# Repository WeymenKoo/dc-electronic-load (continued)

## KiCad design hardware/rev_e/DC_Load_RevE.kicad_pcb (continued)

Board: 2 copper layers, 223 parts (1 on the bottom side), 119 nets, no tracks yet.

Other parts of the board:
H1, H2, H3, H4, H5, H6, H7, H8: MountingHole_3.2mm_M3
HA1, HA2, HA3, HA4: ScrewAccess_D7

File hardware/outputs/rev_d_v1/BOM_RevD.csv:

"Refs","Value","Footprint","MPN","Tolerance","Qty"
"C1,C2,C11,C18,C32","1uF","Capacitor_SMD:C_0603_1608Metric","","","5"
"C3,C6","10uF","Capacitor_SMD:C_0805_2012Metric","","","2"
"C4,C5,C8","22uF 25V","Capacitor_SMD:C_1206_3216Metric","","","3"
"C7,C57","10uF 25V","Capacitor_SMD:C_0805_2012Metric","","","2"
"C9,C12,C14-C17,C19-C21,C23,C27-C29,C31,C34,C51","100nF","Capacitor_SMD:C_0603_1608Metric","","","16"
"C10","1uF 25V","Capacitor_SMD:C_0603_1608Metric","","","1"
"C13","4.7uF","Capacitor_SMD:C_0805_2012Metric","","","1"
"C22","10uF X7R 10V","Capacitor_SMD:C_0805_2012Metric","","","1"
"C24,C25","10nF","Capacitor_SMD:C_0603_1608Metric","","","2"
"C30,C33","10nF C0G","Capacitor_SMD:C_0603_1608Metric","","","2"
"C35","47nF X7R","Capacitor_SMD:C_0603_1608Metric","","","1"
"C41,C42","10nF C0G 50V","Capacitor_SMD:C_0603_1608Metric","","","2"
"C52","100nF X7R","Capacitor_SMD:C_0603_1608Metric","","","1"
"C53-C56","100nF 50V","Capacitor_SMD:C_0603_1608Metric","","","4"
"C58","2.2uF 100V X7S","Capacitor_SMD:C_1206_3216Metric","","","1"
"C101,C201,C301,C401","1nF C0G 50V","Capacitor_SMD:C_0603_1608Metric","","","4"
"D1","USBLC6-2SC6","Package_TO_SOT_SMD:SOT-23-6","","","1"
"D2","LED green","LED_SMD:LED_0603_1608Metric","","","1"
"D3","SS34","Diode_SMD:D_SMA","","","1"
"D4","LED blue","LED_SMD:LED_0603_1608Metric","","","1"
"D5","CC","LED_SMD:LED_0603_1608Metric","","","1"
"D6","CV","LED_SMD:LED_0603_1608Metric","","","1"
"D7","CR","LED_SMD:LED_0603_1608Metric","","","1"
"D8","CP","LED_SMD:LED_0603_1608Metric","","","1"
"D9","BATT","LED_SMD:LED_0603_1608Metric","","","1"
"D10","ON","LED_SMD:LED_0603_1608Metric","","","1"
"D11","FAULT","LED_SMD:LED_0603_1608Metric","","","1"
"D12","REMOTE","LED_SMD:LED_0603_1608Metric","","","1"
"D41,D42","BAT54S","Package_TO_SOT_SMD:SOT-23","","","2"
"D43","BZX84C12","Package_TO_SOT_SMD:SOT-23","","","1"
"D44","BAT54C","Package_TO_SOT_SMD:SOT-23","","","1"
"D45,D101,D201,D301,D401","1N4148WS","Diode_SMD:D_SOD-323","","","5"
"D51","SMCJ70A TVS","Diode_SMD:D_SMC","","","1"
"D102,D202,D302,D402","BZX84C6V8","Package_TO_SOT_SMD:SOT-23","","","4"
"D103,D203,D303,D403","BZX84C15","Package_TO_SOT_SMD:SOT-23","","","4"
"DS1","VOLTS","Display_7Segment:CA56-12SRWA","CC56-12SRWA or 5641AS (common cathode)","","1"
"DS2","AMPS","Display_7Segment:CA56-12SRWA","CC56-12SRWA or 5641AS (common cathode)","","1"
"DS3","SET","Display_7Segment:CA56-12SRWA","CC56-12SRWA or 5641AS (common cathode)","","1"
"ENC1","PEC11L-4120K-S0020","Rotary_Encoder:RotaryEncoder_Alps_EC11E-Switch_Vertical_H20mm","Bourns PEC11L-4120K-S0020","","1"
"F1","15A 58VDC mini blade","Fuse:Fuseholder_Blade_Mini_Keystone_3568","Littelfuse 0997015.WXN","","1"
"J1","USB-C 16P","Connector_USB:USB_C_Receptacle_HRO_TYPE-C-31-M-12","HRO TYPE-C-31-M-12 (16 pin, USB 2.0)","","1"
"J2","FAN 4-pin","Connector_JST:JST_XH_B4B-XH-A_1x04_P2.50mm_Vertical","","","1"
"J3","SWD","Connector_PinHeader_2.54mm:PinHeader_1x05_P2.54mm_Vertical","","","1"
"J4","UART 3V3","Connector_PinHeader_2.54mm:PinHeader_1x03_P2.54mm_Vertical","","","1"
"J5","I2C OLED","Connector_PinHeader_2.54mm:PinHeader_1x04_P2.54mm_Vertical","","","1"
"J6","NTC 10k B3950","Connector_JST:JST_XH_B2B-XH-A_1x02_P2.50mm_Vertical","","","1"
"J7","DUT+","Connector_Wire:SolderWire-2.5sqmm_1x01_D2.4mm_OD3.6mm","","","1"
"J8","DUT-","Connector_Wire:SolderWire-2.5sqmm_1x01_D2.4mm_OD3.6mm","","","1"
"J9","SENSE","Connector_JST:JST_XH_B2B-XH-A_1x02_P2.50mm_Vertical","","","1"
"L1","10uH 2A","Inductor_SMD:L_Bourns_SRN6045TA","SRN6045TA-100M","","1"
"NT1","STAR","NetTie:NetTie-2_SMD_Pad2.0mm","","","1"
"PS1","B0512S-1WR3","dcload:SIP-4_P2.54mm_DCDC_1W","Mornsun B0512S-1WR3 (alt: Murata NXE1S0512MC)","","1"
"Q1","AO3401A","Package_TO_SOT_SMD:SOT-23","","","1"
"Q2,Q3,Q11-Q13","2N7002","Package_TO_SOT_SMD:SOT-23","","","5"
"Q101,Q201,Q301,Q401","IRFP250NPBF","Package_TO_SOT_THT:TO-247-3_Vertical","IRFP250NPBF","","4"
"R1,R2","5.1k","Resistor_SMD:R_0603_1608Metric","","1%","2"
"R3,R10,R13,R16,R24,R33,R37","1k","Resistor_SMD:R_0603_1608Metric","","","7"
"R4","191k","Resistor_SMD:R_0603_1608Metric","","1%","1"
"R5,R54,R58,R62,R69","10.0k","Resistor_SMD:R_0603_1608Metric","","1%","5"
"R6,R8,R65,R105,R205,R305,R405","100k","Resistor_SMD:R_0603_1608Metric","","","7"
"R7,R9,R19-R23,R52,R56,R61,R64,R70","10k","Resistor_SMD:R_0603_1608Metric","","","12"
"R12","4.7R","Resistor_SMD:R_1206_3216Metric","","","1"
"R14,R15","4.7k","Resistor_SMD:R_0603_1608Metric","","","2"
"R17,R18","33k","Resistor_SMD:R_0603_1608Metric","","1%","2"
"R31","15k","Resistor_SMD:R_0603_1608Metric","","0.1%","1"
"R32","1k","Resistor_SMD:R_0603_1608Metric","","0.1%","1"
"R34,R35,R57","100k","Resistor_SMD:R_0603_1608Metric","","1%","3"
"R36,R66","10k","Resistor_SMD:R_0603_1608Metric","","1%","2"
"R41,R67","1M","Resistor_SMD:R_0603_1608Metric","","1%","2"
"R42,R46,R49","10k","Resistor_SMD:R_0603_1608Metric","","0.1%","3"
"R43","110k","Resistor_SMD:R_0603_1608Metric","","0.1%","1"
"R44,R50","1k","Resistor_SMD:R_0603_1608Metric","","1%","2"
"R45,R48","200k","Resistor_SMD:R_1206_3216Metric","","0.1%","2"
"R47","470k","Resistor_SMD:R_0603_1608Metric","","1%","1"
"R51","10.0k","Resistor_SMD:R_0603_1608Metric","","0.1%","1"
"R53","90.9k","Resistor_SMD:R_0603_1608Metric","","1%","1"
"R55","402k","Resistor_SMD:R_0603_1608Metric","","1%","1"
"R59","165k","Resistor_SMD:R_0603_1608Metric","","1%","1"
"R60","47k","Resistor_SMD:R_1206_3216Metric","","1%","1"
"R63","27.4k","Resistor_SMD:R_0603_1608Metric","","1%","1"
"R68","5.90k","Resistor_SMD:R_0603_1608Metric","","1%","1"
"R71","2.2R 1W","Resistor_SMD:R_2512_6332Metric","","1%","1"
"R72,R73","100R","Resistor_SMD:R_1206_3216Metric","","","2"
"R101,R201,R301,R401","4.7k","Resistor_SMD:R_0603_1608Metric","","1%","4"
"R102,R202,R302,R402","22M","Resistor_SMD:R_0603_1608Metric","","5%","4"
"R103,R203,R303,R403","3.3k","Resistor_SMD:R_0603_1608Metric","","1%","4"
"R104,R204,R304,R404","47","Resistor_SMD:R_0603_1608Metric","","1%","4"
"R106,R107,R206,R207,R306,R307,R406,R407","0R2 1W","Resistor_SMD:R_2512_6332Metric","","1%","8"
"R108,R208,R308,R408","10k","Resistor_SMD:R_0603_1608Metric","","0.1% 25ppm","4"
"SW1","RESET","Button_Switch_THT:SW_PUSH_6mm","","","1"
"SW2","BOOT","Button_Switch_THT:SW_PUSH_6mm","","","1"
"SW3","ON/OFF","Button_Switch_THT:SW_PUSH_6mm","","","1"
"SW4","MODE","Button_Switch_THT:SW_PUSH_6mm","","","1"
"SW5","MENU","Button_Switch_THT:SW_PUSH_6mm","","","1"
"TP11","VSET","TestPoint:TestPoint_THTPad_D1.5mm_Drill0.7mm","","","1"
"TP21","ISEN_ADC","TestPoint:TestPoint_THTPad_D1.5mm_Drill0.7mm","","","1"
"TP22","VSEN_ADC","TestPoint:TestPoint_THTPad_D1.5mm_Drill0.7mm","","","1"
"TP31","CV_SET","TestPoint:TestPoint_THTPad_D1.5mm_Drill0.7mm","","","1"
"TP41","KILL","TestPoint:TestPoint_THTPad_D1.5mm_Drill0.7mm","","","1"
"TP51","DUT+","TestPoint:TestPoint_THTPad_D1.5mm_Drill0.7mm","","","1"
"TP52","DRAIN","TestPoint:TestPoint_THTPad_D1.5mm_Drill0.7mm","","","1"
"TP101,TP201,TP301,TP401","GATE","TestPoint:TestPoint_THTPad_D1.5mm_Drill0.7mm","","","4"
"TP102,TP202,TP302,TP402","SOURCE","TestPoint:TestPoint_THTPad_D1.5mm_Drill0.7mm","","","4"
"U1","AP2112K-3.3","Package_TO_SOT_SMD:SOT-23-5","","","1"
"U2","MT3608","Package_TO_SOT_SMD:SOT-23-6","","","1"
"U3","MCP1703A-5002","Package_TO_SOT_SMD:SOT-23","MCP1703AT-5002E/CB","","1"
"U4","STM32G0B1CBT6","Package_QFP:LQFP-48_7x7mm_P0.5mm","STM32G0B1CBT6","","1"
"U5,U6","MAX7219","Package_SO:SOIC-24W_7.5x15.4mm_P1.27mm","MAX7219CWG","","2"
"U7","74AHCT125","Package_SO:SOIC-14_3.9x8.7mm_P1.27mm","","","1"
"U8","ISO7761DW","Package_SO:SOIC-16W_7.5x10.3mm_P1.27mm","ISO7761DW (default-high outputs)","","1"
"U9","MCP4822","Package_SO:SOIC-8_3.9x4.9mm_P1.27mm","MCP4822-E/SN","","1"
"U10","ADS1118","Package_SO:TSSOP-10_3x3mm_P0.5mm","ADS1118IDGSR","","1"
"U11","LT1014","Package_SO:SOIC-16W_7.5x10.3mm_P1.27mm","","","1"
"U12,U13","LT1013","Package_SO:SOIC-8_3.9x4.9mm_P1.27mm","","","2"
"U14","LM339","Package_SO:SOIC-14_3.9x8.7mm_P1.27mm","","","1"

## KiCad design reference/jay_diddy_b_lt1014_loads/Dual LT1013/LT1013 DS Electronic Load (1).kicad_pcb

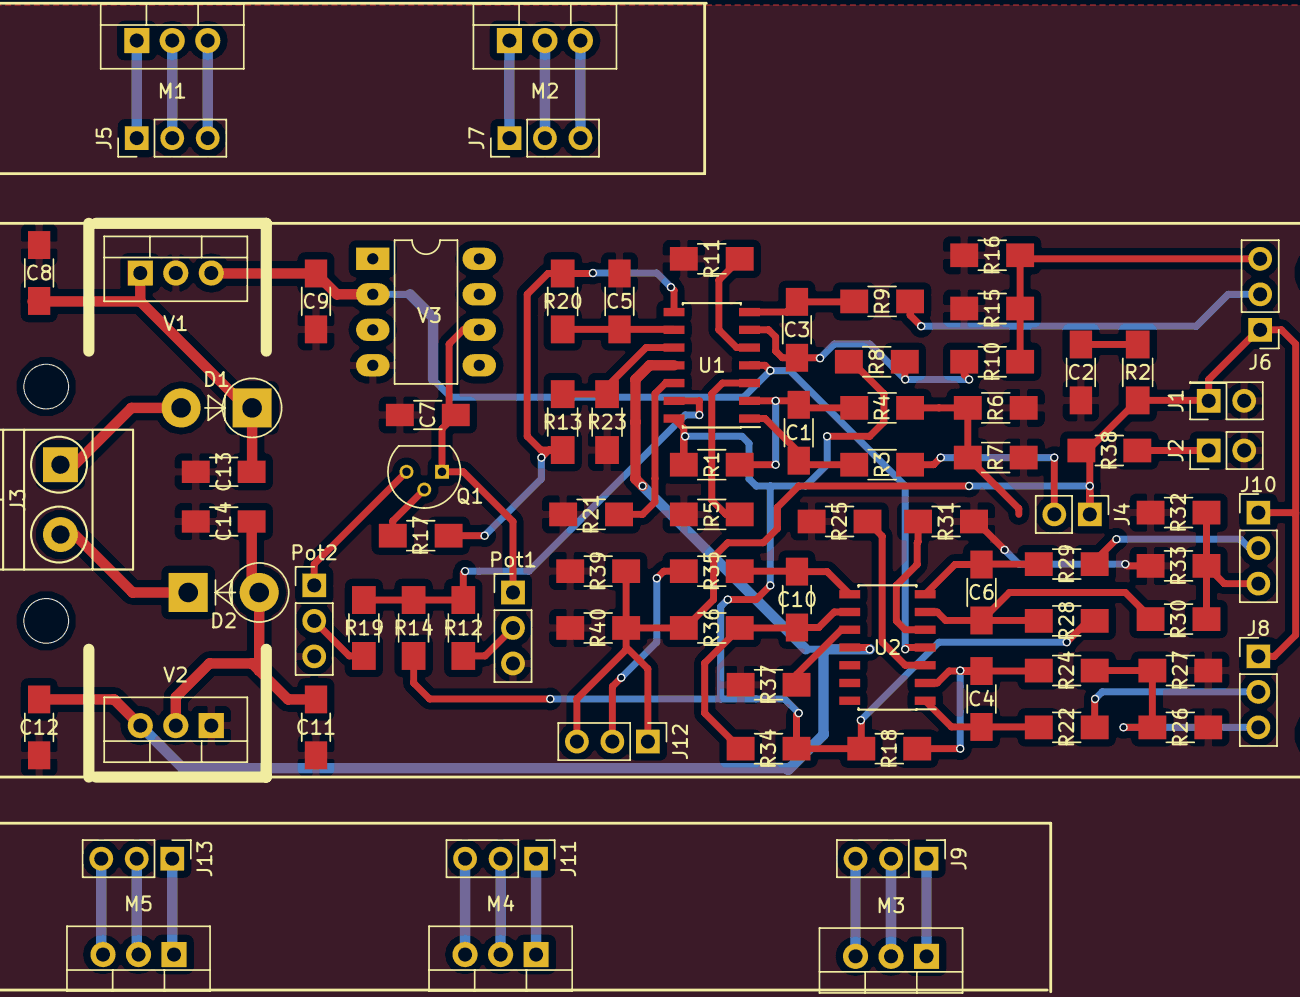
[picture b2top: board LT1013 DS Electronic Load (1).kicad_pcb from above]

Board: 2 copper layers, 82 parts (0 on the bottom side), 60 nets.

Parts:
C1, C3, C4, C6, C10: 220pF; C_1206_HandSoldering
C2, C11: 2.2uF; C_1206_HandSoldering
C5, C7, C9: 0.1uF; C_1206_HandSoldering
C8: 0.33uF; C_1206_HandSoldering
C12: 1uF; C_1206_HandSoldering
C13, C14: 220uF; C_1206_HandSoldering
D1: 1N4002; D_5W_P5.08mm_Vertical_AnodeUp
D2: 1N4002; D_5W_P5.08mm_Vertical_KathodeUp
J1: Conn_01x02; Socket_Strip_Straight_2x01_Pitch2.54mm
J2: Conn_01x02; Pin_Header_Straight_1x02_Pitch2.54mm
J3: Screw_Terminal_01x02; TerminalBlock_Pheonix_MKDS1.5-2pol
J4: Conn_01x03; Pin_Header_Straight_1x02_Pitch2.54mm
J5, J6, J7, J8, J9, J10, J11, J12, J13: Conn_01x03; Pin_Header_Straight_1x03_Pitch2.54mm
M1, M2, M3, M4, M5: IRF530; TO-220-3_Vertical
Pot1, Pot2: 10K; Pin_Header_Straight_1x03_Pitch2.54mm
Q1: 2N3906; TO-92_Molded_Narrow
R1, R8, R13, R18, R21, R28, R34: 33K; R_1206_HandSoldering
R2: 2.2; R_1206_HandSoldering
R3, R9, R22, R29, R35: 100; R_1206_HandSoldering
R4, R5, R10, R11, R24, R25, R30, R31, R36, R37: 3K3; R_1206_HandSoldering
R6, R7, R15, R16, R26, R27, R32, R33, R39, R40: 0.2; R_1206_HandSoldering
R12, R14, R19: 100K; R_1206_HandSoldering
R17, R20, R23: 15K; R_1206_HandSoldering
R38: 51R; R_1206_HandSoldering
U1, U2: LT1013; SOIC-14_3.9x8.7mm_Pitch1.27mm
V1: L7809; TO-220-3_Vertical
V2: LM7909_TO220; TO-220-3_Vertical
V3: LT1019_Voltage_Reference; DIP-8_W7.62mm_LongPads

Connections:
/+9V: C9.1, U1.4, U2.4, V1.3, V3.2
/-9v: C12.1, U1.11, U2.11, V2.3
/Vref: C7.1, Pot1.1, Q1.1, V3.6
GND: C2.2, C5.2, C7.2, C8.2, C9.2, C11.2, C12.2, C13.1, C14.2, J1.2, J2.2, Pot1.3, Pot2.3, R5.2, R6.2, R7.2, R11.2, R15.2, R16.2, R21.1, R23.2, R25.2, R26.2, R27.2, R31.2, R32.2, R33.2, R37.2, R39.2, R40.2, V1.2, V2.1, V3.4
unnamed: C1.1, R3.2, U1.1
unnamed: C1.2, R1.2, R4.1, U1.2
unnamed: C2.1, R2.2
unnamed: C3.1, R9.2, U1.7
unnamed: C3.2, R8.2, R10.1, U1.6
unnamed: C4.1, R22.2, U2.1
unnamed: C4.2, R18.2, R24.1, U2.2
unnamed: C5.1, R20.2, U1.9
unnamed: C6.1, R29.2, U2.7
unnamed: C6.2, R28.2, R30.1, U2.6
unnamed: C10.1, R35.2, U2.8
unnamed: C10.2, R34.2, R36.1, U2.9
unnamed: C11.1, C14.1, D2.2, V2.2
unnamed: C8.1, C13.2, D1.1, V1.1
unnamed: D1.2, J3.1
unnamed: D2.1, J3.2
unnamed: J1.1, J4.1, J6.1, J8.1, J10.1, J12.1, J12.3, R2.1, R36.2, R38.2, R39.1, R40.1
unnamed: J2.1, R38.1
unnamed: J4.2, R3.1
unnamed: R4.2, R6.1, R7.1
unnamed: J5.1, M1.1
unnamed: J5.2, M1.2
unnamed: J5.3, M1.3
unnamed: J6.2, R9.1
unnamed: J6.3, R10.2, R15.1, R16.1
unnamed: J7.1, M2.1
unnamed: J7.2, M2.2
unnamed: J7.3, M2.3
unnamed: J8.2, R22.1
unnamed: J8.3, R24.2, R26.1, R27.1
unnamed: J9.1, M3.1
unnamed: J9.2, M3.2
unnamed: J9.3, M3.3
unnamed: J10.2, R29.1
unnamed: J10.3, R30.2, R32.1, R33.1
unnamed: J11.1, M4.1
unnamed: J11.2, M4.2
unnamed: J11.3, M4.3
unnamed: J12.2, R35.1
unnamed: J13.1, M5.1
unnamed: J13.2, M5.2
unnamed: J13.3, M5.3
unnamed: Pot1.2, R12.2
unnamed: Pot2.1, Q1.3
unnamed: Pot2.2, R19.2
unnamed: Q1.2, R17.1
unnamed: R1.1, R8.1, R14.1, R18.1, R28.1, R34.1, U1.14
unnamed: R5.1, U1.3
unnamed: R11.1, U1.5
unnamed: R12.1, R14.2, R19.1, U1.13
unnamed: R13.1, R17.2, R20.1, U1.8
unnamed: R13.2, R23.1, U1.10
unnamed: R21.2, U1.12
unnamed: R25.1, U2.3
unnamed: R31.1, U2.5
unnamed: R37.1, U2.10

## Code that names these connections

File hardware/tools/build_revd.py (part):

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    esd.fpos = {'Reference': (103, 100), 'Value': (103, 103)}
    s.wire((70, dp2[1]), (70, 110), (86, 110), (86, esd.pin('3')[1]), esd.pin('3'), color=C_USB)
    s.wire((72, dm2[1]), (72, esd.pin('1')[1]), esd.pin('1'), color=C_USB)
    s.wire(esd.pin('6'), (112, esd.pin('6')[1]), color=C_USB); s.hier('USB_DM', 112, esd.pin('6')[1], ang=0, shape='bidirectional', color=C_USB)
    s.wire(esd.pin('4'), (112, esd.pin('4')[1]), color=C_USB); s.hier('USB_DP', 112, esd.pin('4')[1], ang=0, shape='bidirectional', color=C_USB)
    s.rail('VBUS', esd.pin('5')[0], esd.pin('5')[1]); s.rail('DGND', esd.pin('2')[0], esd.pin('2')[1])
    s.nc(*j.pin('A8')); s.nc(*j.pin('B8'))
    g, sh = j.pin('A1'), j.pin('SH')
    s.wire(g, (g[0], 112), (62, 112)); s.rail('DGND', g[0], 112); s.rail('FLAG', 62, 112)
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    s.begin_block('D   Ground star point and the isolation barrier rating', FILL_A)
    nt = s.part('Device:NetTie_2', 'NT1', 'STAR', 60, 190, fp='NetTie:NetTie-2_SMD_Pad2.0mm')
    nt.fpos = {'Reference': (60, 186.2, 'center'), 'Value': (60, 193.8, 'center')}
    s.wire(nt.pin('1'), (50, 190), (50, 196)); s.rail('AGND', 50, 196)
    s.wire(nt.pin('2'), (70, 190), (70, 196)); s.rail('PGND', 70, 196); s.rail('FLAG', 76, 190)
    s.wire((70, 190), (76, 190))
    s.note('AGND (analog reference) meets PGND (DUT minus, source\n'
           'resistors) ONLY at NT1. Place NT1 at the centre of the four\n'
           'Rs bottom pads: 1 mR between an Rs and NT1 is 10 mV at 10 A\n'
           '(4 % of full scale).\n\n'
           'Barrier: DGND side to AGND / PGND side. Rated 150 V DC\n'
           'working (IEC 60664-1 functional, PD2, material group IIIb:\n'
           '1.6 mm creepage; IPC-2221B B2: 0.7 mm). Board rule 4 mm,\n'
           'no copper crosses on any layer. ISO7761 (5 kVrms, 8 mm) and\n'
           'the 3 kVDC DC-DC exceed it by far. Float the load on a DUT\n'
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    u = s.ic('Regulator_Linear:AP2112K-3.3', 'U1', 'AP2112K-3.3', 192, y + 2.54, 10); u.fpos = {'Reference': (192, y - 9.5, 'center'), 'Value': (192, y - 6.5, 'center')}
    vin, en, gnd, vout = u.pin('1'), u.pin('3'), u.pin('2'), u.pin('5')
    s.wire(en, (180, en[1]), (180, y))
    s.rail('DGND', gnd[0], gnd[1]); s.nc(*u.pin('4'))
    s.wire(vout, (244, y), color=C_PWR); s.rail('+3V3', 244, y)
    c = s.cap('C2', '1uF', 210, y + 6); s.wire((210, y), top(c)); s.rail('DGND', 210, bot(c)[1])
    r = s.res('R3', '1k', 228, y + 6); s.wire((228, y), top(r))
    d = s.led('D2', 'LED green', 228, y + 16); s.wire(bot(r), d.pin('2')); s.wire(d.pin('1'), (228, y + 23)); s.rail('DGND', 228, y + 23)
    s.note('+3V3: MCU, isolator side 1, pull-ups, LED. 60 mA.', 170, 94)
    # ---- branch 2: 12 V fan supply
    y = 108
    s.wire((T, y), (210.19, y), color=C_PWR)
    c = s.cap('C3', '10uF', 172, y + 6, fp=C0805); s.wire((172, y), top(c)); s.rail('DGND', 172, bot(c)[1])
    u = s.ic('Regulator_Switching:MT3608', 'U2', 'MT3608', 200, y + 16, 10); u.fpos = {'Reference': (200, y + 5.5, 'center'), 'Value': (209.5, y + 24.5)}
    pin_in, pen, sw, fb, pgnd = u.pin('5'), u.pin('4'), u.pin('1'), u.pin('3'), u.pin('2')
    s.wire((190, y), (190, pin_in[1]), pin_in)
    l = s.part('Device:L', 'L1', '10uH 2A', 214, y, rot=90, fp='Inductor_SMD:L_Bourns_SRN6045TA', f={'MPN': 'SRN6045TA-100M'})
    l.fpos = {'Reference': (214, y - 2.6, 'center'), 'Value': (214, y + 3.3, 'center')}
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    rt = s.res('R4', '191k', 236, y + 7.27, tol='1%'); s.wire((236, y), top(rt))
    s.wire(fb, (236, fb[1])); s.wire(bot(rt), (236, fb[1]))
    rb = s.res('R5', '10.0k', 236, fb[1] + 7.46, tol='1%'); s.wire((236, fb[1]), top(rb)); s.rail('DGND', 236, bot(rb)[1])
    s.rail('DGND', pgnd[0], pgnd[1]); s.nc(*u.pin('6'))
    s.wire(pen, (188, pen[1]), (188, y + 32), (176, y + 32)); s.hier('FAN_EN', 176, y + 32, ang=180)
    rpd = s.res('R6', '100k', 188, y + 37); s.wire((188, y + 32), top(rpd)); s.rail('DGND', 188, bot(rpd)[1])
    s.note('+12V_FAN: 0.6 V x (1 + 191k / 10k) = 12.06 V, 0.3 A max = 0.8 A from USB.\nEN low: output sits at VBUS minus a diode and Q1 (block C) is off.', 170, 166)
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    rpu = s.res('R7', '10k', X0, Y0 - 10.81); s.rail('+12V_FAN', X0, top(rpu)[1])
    qn = s.fet(Q2N, 'Q2', '2N7002', X0 - 20, Y0 + 1)
    s.wire(gate, (X0, Y0 - 7), (qn.pin('3')[0], Y0 - 7), qn.pin('3'))
    s.rail('DGND', qn.pin('2')[0], qn.pin('2')[1])
    s.wire(qn.pin('1'), (X0 - 36, qn.pin('1')[1])); s.hier('FAN_EN', X0 - 36, qn.pin('1')[1], ang=180)
    rpd2 = s.res('R8', '100k', X0 - 30, Y0 + 7); s.wire((X0 - 30, qn.pin('1')[1]), top(rpd2)); s.rail('DGND', X0 - 30, bot(rpd2)[1])
    s.wire(p3, (X0 + 12, p3[1]), (X0 + 12, Y0 + 38), (X0 + 6, Y0 + 38))
    rpu2 = s.res('R9', '10k', X0 + 6, Y0 + 34.19, fl=True); s.rail('+3V3', X0 + 6, top(rpu2)[1])
    rs = s.res('R10', '1k', X0 - 4, Y0 + 38, h=True); s.wire((X0 + 6, Y0 + 38), rgt(rs)); s.wire(lft(rs), (X0 - 18, Y0 + 38)); s.hier('FAN_TACH', X0 - 18, Y0 + 38, ang=180, shape='output')
    s.wire(p4, (X0 + 16, p4[1]), (X0 + 16, Y0 + 60))
    qpwm = s.fet(Q2N, 'Q3', '2N7002', X0 + 13.46, Y0 + 65.08)
    s.rail('DGND', qpwm.pin('2')[0], qpwm.pin('2')[1])
    s.wire(qpwm.pin('1'), (X0 - 18, qpwm.pin('1')[1])); s.hier('FAN_PWM', X0 - 18, qpwm.pin('1')[1], ang=180)
    rpu3 = s.res('R11', '10k DNP', X0 + 6, Y0 + 56.19, dnp=True, fl=True); s.wire((X0 + 16, Y0 + 60), bot(rpu3)); s.rail('VBUS', X0 + 6, top(rpu3)[1])
    s.note('J2 = PC fan pinout: 1 GND, 2 +12 V,\n'
           '3 tach (open collector, pulled to 3.3 V),\n'
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    H, L = 'hier', 'label'
    # name -> (label, kind, shape, colour)
    plan = {
        'PA0': ('CC1_SENSE', H, 'input', None), 'PA1': ('CC2_SENSE', H, 'input', None),
        'PA4': ('~{CS_DAC}', H, 'output', C_SPI), 'PA5': ('SPI1_SCK', H, 'output', C_SPI), 'PA6': ('SPI1_MISO', H, 'input', C_SPI), 'PA7': ('SPI1_MOSI', H, 'output', C_SPI),
        'PB0': ('~{CS_ADC}', H, 'output', C_SPI), 'PB1': ('LOAD_OFF', H, 'output', C_PROT),
        'PB12': ('~{DISP_CS}', H, 'output', None), 'PB13': ('SPI2_SCK', H, 'output', None), 'PB15': ('SPI2_MOSI', H, 'output', None),
        'PC6': ('LED_STATUS', L, None, None), 'PA9/UCPD1_DBCC1': ('UART_TX', L, None, None), 'PA10/UCPD1_DBCC2': ('UART_RX', L, None, None),
        'PA9/PA11': ('USB_DM', H, 'bidirectional', C_USB), 'PA10/PA12': ('USB_DP', H, 'bidirectional', C_USB),
        'PA13': ('SWDIO', L, None, None), 'PA14': ('SWCLK_BOOT0', L, None, None),
        'PB3': ('ENC_SW', H, 'input', None), 'PB4': ('ENC_A', H, 'input', None), 'PB5': ('ENC_B', H, 'input', None),
        'PB6': ('I2C_SCL', L, None, None), 'PB7': ('I2C_SDA', L, None, None), 'PB8': ('FAN_TACH', H, 'input', None), 'PB9': ('FAN_PWM', H, 'output', None),
        'PD0': ('BTN_ON', H, 'input', None), 'PD1': ('BTN_MODE', H, 'input', None), 'PD2': ('BTN_MENU', H, 'input', None),
        'PD3': ('FAN_EN', H, 'output', None), 'PF2': ('NRST', L, None, None),
    }
    names = {}
    for sub in find(u.sym, 'symbol'):
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    s.wire(vref, (vref[0] - 8, vref[1]), (vref[0] - 8, vref[1] - 8), color=C_PWR); s.rail('+3V3', vref[0] - 8, vref[1] - 8)
    s.rail('DGND', vss[0], vss[1])
    s.note('Pin plan (STM32G0B1CBT6, LQFP48)\n'
           'SPI1   PA5 SCK, PA6 MISO, PA7 MOSI, PA4 /CS DAC, PB0 /CS ADC, PB1 LOAD_OFF (isolator)\n'
           'SPI2   PB13 SCK, PB15 MOSI, PB12 /CS = MAX7219 LOAD (display chain, via 74AHCT125)\n'
           'TIM3   PB4 / PB5 encoder, PB3 push.  TIM17 PB9 fan PWM, TIM16 PB8 tach, PD3 FAN_EN\n'
           'ADC    PA0 / PA1 = CC1 / CC2.  USB PA11 DM, PA12 DP, crystal-less (CRS)\n'
           'USART1 PA9 / PA10 debug.  I2C1 PB6 / PB7 OLED.  PD0 ON/OFF, PD1 MODE, PD2 MENU, PC6 LED\n'
           'Why not the STM32F103RBT6 of Rev B: no USB DFU in its ROM (USART only), needs a\n'
           'crystal, no CRS, same LQFP64 size. The G0B1 is cheaper, smaller, and its ROM DFU\n'
           'removes the second USB port.\n'
           'Spare: PA2, PA3, PA8, PA15, PB2, PB10, PB11, PB14, PC7, PC13-PC15, PF0, PF1 (NC).', 48, 236)
    s.end_block()
    # ------------------------------------------------------------ support blocks
    bx = 262
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    s.begin_block('C   Reset, BOOT0 (DFU), SWD', FILL_D)
    y0 = 104
    sw = s.part('Switch:SW_Push', 'SW1', 'RESET', bx + 28, y0, fp='Button_Switch_THT:SW_PUSH_6mm'); sw.fpos = {'Reference': (bx + 28, y0 - 4.5, 'center'), 'Value': (bx + 28, y0 + 4.5, 'center')}
    s.wire(sw.pin('1'), (bx + 12, y0)); s.lab('NRST', bx + 12, y0, ang=180); s.wire(sw.pin('2'), (bx + 42, y0)); s.rail('DGND', bx + 42, y0)
    c = s.cap('C19', '100nF', bx + 16, y0 + 7); s.wire((bx + 16, y0), top(c)); s.rail('DGND', bx + 16, bot(c)[1])
    sw = s.part('Switch:SW_Push', 'SW2', 'BOOT', bx + 28, y0 + 24, fp='Button_Switch_THT:SW_PUSH_6mm'); sw.fpos = {'Reference': (bx + 28, y0 + 19.5, 'center'), 'Value': (bx + 28, y0 + 28.5, 'center')}
    r = s.res('R13', '1k', bx + 44, y0 + 24, h=True); s.wire(sw.pin('2'), lft(r)); s.wire(rgt(r), (bx + 58, y0 + 24)); s.rail('+3V3', bx + 58, y0 + 24)
    s.wire(sw.pin('1'), (bx + 12, y0 + 24)); s.lab('SWCLK_BOOT0', bx + 12, y0 + 24, ang=180)
    jh = s.part('Connector_Generic:Conn_01x05', 'J3', 'SWD', bx + 110, y0 + 12, fp=PH % 5, f={'Note': '1 +3V3  2 SWDIO  3 SWCLK  4 NRST  5 GND'})
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
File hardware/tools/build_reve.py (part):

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FFC_MPN = '2x6 shrouded box header 2.54 mm, BOOMELE 2.54-2*6P (LCSC C9136). Pin n = ribbon conductor n'
STUD = 'MountingHole:MountingHole_4.3mm_M4_Pad'                   # M4 bolt through a plated pad: ring lug on the DUT lead, nut and washers
# J10 / J11 pin assignment (pin 1 to pin 1 through the cable). Power pins at the ends keep the schematic crossing-free.
LINK_PINS = {1: 'VBUS', 2: 'VBUS', 3: '+3V3', 4: 'SPI1_SCK', 5: 'SPI1_MOSI', 6: 'SPI1_MISO', 7: '~{CS_DAC}', 8: '~{CS_ADC}', 9: 'LOAD_OFF',
             10: 'DGND', 11: 'DGND', 12: 'DGND'}
LINK_SHAPE = {'SPI1_SCK': 'input', 'SPI1_MOSI': 'input', 'SPI1_MISO': 'output', '~{CS_DAC}': 'input', '~{CS_ADC}': 'input', 'LOAD_OFF': 'input'}

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    esd.fpos = {'Reference': (103, 100), 'Value': (103, 103)}
    s.wire((70, dp2[1]), (70, 110), (86, 110), (86, esd.pin('3')[1]), esd.pin('3'), color=C_USB)
    s.wire((72, dm2[1]), (72, esd.pin('1')[1]), esd.pin('1'), color=C_USB)
    s.wire(esd.pin('6'), (112, esd.pin('6')[1]), color=C_USB); s.hier('USB_DM', 112, esd.pin('6')[1], ang=0, shape='bidirectional', color=C_USB)
    s.wire(esd.pin('4'), (112, esd.pin('4')[1]), color=C_USB); s.hier('USB_DP', 112, esd.pin('4')[1], ang=0, shape='bidirectional', color=C_USB)
    s.rail('VBUS', esd.pin('5')[0], esd.pin('5')[1]); s.rail('DGND', esd.pin('2')[0], esd.pin('2')[1])
    s.nc(*j.pin('A8')); s.nc(*j.pin('B8'))
    g, sh = j.pin('A1'), j.pin('SH')
    s.wire(g, (g[0], 112), (62, 112)); s.rail('DGND', g[0], 112); s.rail('FLAG', 62, 112)
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    s.begin_block('D   Ground star point and the isolation barrier rating', FILL_A)
    nt = s.part('Device:NetTie_2', 'NT1', 'STAR', 60, 190, fp='NetTie:NetTie-2_SMD_Pad2.0mm')
    nt.fpos = {'Reference': (60, 186.2, 'center'), 'Value': (60, 193.8, 'center')}
    s.wire(nt.pin('1'), (50, 190), (50, 196)); s.rail('AGND', 50, 196)
    s.wire(nt.pin('2'), (70, 190), (70, 196)); s.rail('PGND', 70, 196); s.rail('FLAG', 76, 190)
    s.wire((70, 190), (76, 190))
    s.note('AGND (analog reference) meets PGND (DUT minus, source\n'
           'resistors) ONLY at NT1. Place NT1 at the centre of the four\n'
           'Rs bottom pads: 1 mR between an Rs and NT1 is 10 mV at 10 A\n'
           '(4 % of full scale).\n\n'
           'Barrier: DGND side to AGND / PGND side. Rated 150 V DC\n'
           'working (IEC 60664-1 functional, PD2, material group IIIb:\n'
           '1.6 mm creepage; IPC-2221B B2: 0.7 mm). Board rule 4 mm,\n'
           'no copper crosses on any layer. CA-IS3761 (5 kVrms, 8 mm) and\n'
           'the 1.5 kVDC DC-DC exceed it by far. Float the load on a DUT\n'
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    u = s.ic('Regulator_Linear:AP2112K-3.3', 'U1', 'AP2112K-3.3', 192, y + 2.54, 10, f={'LCSC': 'C23380830'}); u.fpos = {'Reference': (192, y - 9.5, 'center'), 'Value': (192, y - 6.5, 'center')}
    vin, en, gnd, vout = u.pin('1'), u.pin('3'), u.pin('2'), u.pin('5')
    s.wire(en, (180, en[1]), (180, y))
    s.rail('DGND', gnd[0], gnd[1]); s.nc(*u.pin('4'))
    s.wire(vout, (244, y), color=C_PWR); s.rail('+3V3', 244, y)
    c = s.cap('C2', '1uF', 210, y + 6); s.wire((210, y), top(c)); s.rail('DGND', 210, bot(c)[1])
    r = s.res('R3', '1k', 228, y + 6); s.wire((228, y), top(r))
    d = s.led('D2', 'LED green', 228, y + 16, f={'MPN': 'KT-0603G', 'LCSC': 'C12624'}); s.wire(bot(r), d.pin('2')); s.wire(d.pin('1'), (228, y + 23)); s.rail('DGND', 228, y + 23)
    s.note('+3V3: MCU, isolator side 1, pull-ups, LED. 60 mA.', 170, 94)
    # ---- branch 2: isolated analog supply
    y = 108
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    c3 = s.cap('C3', '10uF', X0 + 33, Y0 - 2, fp=C0805, fl=True); s.rail('VBUS', X0 + 33, top(c3)[1]); s.rail('DGND', X0 + 33, bot(c3)[1])
    qn = s.fet(Q2N, 'Q2', '2N7002', X0 - 20, Y0 + 1, f={'LCSC': 'C8545'})
    s.wire(gate, (X0, Y0 - 7), (qn.pin('3')[0], Y0 - 7), qn.pin('3'))
    s.rail('DGND', qn.pin('2')[0], qn.pin('2')[1])
    s.wire(qn.pin('1'), (X0 - 36, qn.pin('1')[1])); s.hier('FAN_EN', X0 - 36, qn.pin('1')[1], ang=180)
    rpd2 = s.res('R8', '100k', X0 - 30, Y0 + 7); s.wire((X0 - 30, qn.pin('1')[1]), top(rpd2)); s.rail('DGND', X0 - 30, bot(rpd2)[1])
    s.wire(p3, (X0 + 12, p3[1]), (X0 + 12, Y0 + 38), (X0 + 6, Y0 + 38))
    rpu2 = s.res('R9', '10k', X0 + 6, Y0 + 34.19, fl=True); s.rail('+3V3', X0 + 6, top(rpu2)[1])
    rs = s.res('R10', '1k', X0 - 4, Y0 + 38, h=True); s.wire((X0 + 6, Y0 + 38), rgt(rs)); s.wire(lft(rs), (X0 - 18, Y0 + 38)); s.hier('FAN_TACH', X0 - 18, Y0 + 38, ang=180, shape='output')
    s.wire(p4, (X0 + 16, p4[1]), (X0 + 16, Y0 + 60))
    qpwm = s.fet(Q2N, 'Q3', '2N7002', X0 + 13.46, Y0 + 65.08, f={'LCSC': 'C8545'})
    s.rail('DGND', qpwm.pin('2')[0], qpwm.pin('2')[1])
    s.wire(qpwm.pin('1'), (X0 - 18, qpwm.pin('1')[1])); s.hier('FAN_PWM', X0 - 18, qpwm.pin('1')[1], ang=180)
    rpu3 = s.res('R11', '10k DNP', X0 + 6, Y0 + 56.19, dnp=True, fl=True); s.wire((X0 + 16, Y0 + 60), bot(rpu3)); s.rail('VBUS', X0 + 6, top(rpu3)[1])
    s.note('J2 = PC fan pinout on 5 V: 1 GND, 2 +5 V\n'
           'switched by Q1, 3 tach (open collector,\n'
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    H, L = 'hier', 'label'
    # name -> (label, kind, shape, colour)
    plan = {
        'PA0': ('CC1_SENSE', H, 'input', None), 'PA1': ('CC2_SENSE', H, 'input', None),
        'PA4': ('~{CS_DAC}', H, 'output', C_SPI), 'PA5': ('SPI1_SCK', H, 'output', C_SPI), 'PA6': ('SPI1_MISO', H, 'input', C_SPI), 'PA7': ('SPI1_MOSI', H, 'output', C_SPI),
        'PB0': ('~{CS_ADC}', H, 'output', C_SPI), 'PB1': ('LOAD_OFF', H, 'output', C_PROT),
        'PA8': ('LED_ON', H, 'output', None), 'PC7': ('LED_FAULT', H, 'output', None),
        'PC6': ('LED_STATUS', L, None, None), 'PA9/UCPD1_DBCC1': ('UART_TX', L, None, None), 'PA10/UCPD1_DBCC2': ('UART_RX', L, None, None),
        'PA9/PA11': ('USB_DM', H, 'bidirectional', C_USB), 'PA10/PA12': ('USB_DP', H, 'bidirectional', C_USB),
        'PA13': ('SWDIO', L, None, None), 'PA14': ('SWCLK_BOOT0', L, None, None),
        'PB3': ('ENC_SW', H, 'input', None), 'PB4': ('ENC_A', H, 'input', None), 'PB5': ('ENC_B', H, 'input', None),
        'PB6': ('I2C_SCL', H, 'bidirectional', None), 'PB7': ('I2C_SDA', H, 'bidirectional', None), 'PB8': ('FAN_TACH', H, 'input', None), 'PB9': ('FAN_PWM', H, 'output', None),
        'PD0': ('BTN_ON', H, 'input', None), 'PD1': ('BTN_MODE', H, 'input', None), 'PD2': ('BTN_MENU', H, 'input', None),
        'PD3': ('FAN_EN', H, 'output', None), 'PF2': ('NRST', L, None, None),
    }
    names = {}
    for sub in find(u.sym, 'symbol'):
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    s.wire(vref, (vref[0] - 8, vref[1]), (vref[0] - 8, vref[1] - 8), color=C_PWR); s.rail('+3V3', vref[0] - 8, vref[1] - 8)
    s.rail('DGND', vss[0], vss[1])
    s.note('Pin plan (STM32G0B1RBT6, LQFP64; the CBT6 of Rev D is not stocked at JLC, same die, same pin names)\n'
           'SPI1   PA5 SCK, PA6 MISO, PA7 MOSI, PA4 /CS DAC, PB0 /CS ADC, PB1 LOAD_OFF (isolator)\n'
           'I2C1   PB6 SCL, PB7 SDA: the OLED module (page 4). No display driver, no level shifter.\n'
           'TIM3   PB4 / PB5 encoder, PB3 push.  TIM17 PB9 fan PWM, TIM16 PB8 tach, PD3 FAN_EN\n'
           'ADC    PA0 / PA1 = CC1 / CC2.  USB PA11 DM, PA12 DP, crystal-less (CRS)\n'
           'USART1 PA9 / PA10 debug.  PD0 ON/OFF, PD1 MODE, PD2 MENU.  PC6 heartbeat LED, PA8 ON LED, PC7 FAULT LED\n'
           'Why not the STM32F103C8T6 ($1.50 at JLC): no USB DFU in its ROM (USART only), needs a crystal, no\n'
           'CRS; the G0B1 ROM DFU is what removes the second USB port. Swap it in if you have an ST-Link and F103s.\n'
           'Spare: PA2, PA3, PA15, PB2, PB10-PB15, PC0-PC5, PC8-PC15, PD4-PD9, PF0, PF1 (NC).', 48, 236)
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    s.begin_block('C   Reset, BOOT0 (DFU), SWD', FILL_D)
    y0 = 104
    sw = s.part('Switch:SW_Push', 'SW1', 'RESET', bx + 28, y0, fp='Button_Switch_THT:SW_PUSH_6mm', f={'MPN': 'KH-6X6X5H-TJ', 'LCSC': 'C2837515'}); sw.fpos = {'Reference': (bx + 28, y0 - 4.5, 'center'), 'Value': (bx + 28, y0 + 4.5, 'center')}
    s.wire(sw.pin('1'), (bx + 12, y0)); s.lab('NRST', bx + 12, y0, ang=180); s.wire(sw.pin('2'), (bx + 42, y0)); s.rail('DGND', bx + 42, y0)
    c = s.cap('C19', '100nF', bx + 16, y0 + 7); s.wire((bx + 16, y0), top(c)); s.rail('DGND', bx + 16, bot(c)[1])
    sw = s.part('Switch:SW_Push', 'SW2', 'BOOT', bx + 28, y0 + 24, fp='Button_Switch_THT:SW_PUSH_6mm', f={'MPN': 'KH-6X6X5H-TJ', 'LCSC': 'C2837515'}); sw.fpos = {'Reference': (bx + 28, y0 + 19.5, 'center'), 'Value': (bx + 28, y0 + 28.5, 'center')}
    r = s.res('R13', '1k', bx + 44, y0 + 24, h=True); s.wire(sw.pin('2'), lft(r)); s.wire(rgt(r), (bx + 58, y0 + 24)); s.rail('+3V3', bx + 58, y0 + 24)
    s.wire(sw.pin('1'), (bx + 12, y0 + 24)); s.lab('SWCLK_BOOT0', bx + 12, y0 + 24, ang=180)
    jh = s.part('Connector_Generic:Conn_01x05', 'J3', 'SWD', bx + 110, y0 + 12, fp=PH % 5, f={'Note': '1 +3V3  2 SWDIO  3 SWCLK  4 NRST  5 GND', 'MPN': 'B-2100S05P-A110', 'LCSC': 'C124379'})
    jh.fpos = {'Reference': (bx + 110, y0 + 3, 'center'), 'Value': (bx + 110, y0 + 21.5, 'center')}
    for n, name in (('2', 'SWDIO'), ('3', 'SWCLK_BOOT0'), ('4', 'NRST')):
        p = jh.pin(n); s.wire(p, (p[0] - 8, p[1])); s.lab(name, p[0] - 8, p[1], ang=180)
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
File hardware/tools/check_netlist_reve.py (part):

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            pins[(n.get('ref'), n.get('pin'))] = netname(net.get('name'))
            fn = n.get('pinfunction')
            if fn:
                for part in fn.split('/'):                       # 'PA9/PA11' -> PA9 and PA11; 'VBAT_4' -> VBAT
                    part = re.sub(r'_\d+$', '', part)
                    pins.setdefault((n.get('ref'), '@' + part), netname(net.get('name')))   # ('U4', '@PA5') by pin name; the real PA9 pin comes before the PA9/PA11 remap alias
    return pins


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        return k.get((ref, pin), 'NONE:%s.%s' % (ref, pin))
    same = [
        # isolator channels: MCU -> side 1 -> side 2 -> DAC / ADC
        (('U4', '@PA5'), ('J10', '4'), 'SPI1_SCK to J10'), (('J11', '4'), ('U8', '2'), 'J11 to INA'), (('U8', '15'), ('U9', '3'), 'OUTA = DAC SCK'), (('U8', '15'), ('U10', '1'), 'OUTA = ADC SCLK'),
        (('U4', '@PA7'), ('J10', '5'), 'SPI1_MOSI to J10'), (('J11', '5'), ('U8', '3'), 'J11 to INB'), (('U8', '14'), ('U9', '4'), 'OUTB = DAC SDI'), (('U8', '14'), ('U10', '10'), 'OUTB = ADC DIN'),
        (('U4', '@PA4'), ('J10', '7'), '/CS_DAC to J10'), (('J11', '7'), ('U8', '4'), 'J11 to INC'), (('U8', '13'), ('U9', '2'), 'OUTC = DAC /CS'),
        (('U4', '@PB0'), ('J10', '8'), '/CS_ADC to J10'), (('J11', '8'), ('U8', '5'), 'J11 to IND'), (('U8', '12'), ('U10', '2'), 'OUTD = ADC /CS'),
        (('U4', '@PB1'), ('J10', '9'), 'LOAD_OFF to J10'), (('J11', '9'), ('U8', '6'), 'J11 to INE'), (('U8', '11'), ('D44', '2'), 'OUTE = LOAD_OFF_ISO into the OFF diode-OR'),
        (('U10', '9'), ('U8', '10'), 'ADC DOUT to INF'), (('U8', '7'), ('J11', '6'), 'OUTF to J11'), (('J10', '6'), ('U4', '@PA6'), 'J10 = SPI1_MISO'),
        (('R21', '2'), ('U8', '4'), 'pull-up on /CS_DAC'), (('R22', '2'), ('U8', '5'), 'pull-up on /CS_ADC'), (('R23', '2'), ('U8', '6'), 'pull-up on LOAD_OFF'),
        # DAC / ADC analog connections
        (('U9', '8'), ('R31', '1'), 'DAC A = LOAD_CTRL into the 15k'), (('U9', '6'), ('R33', '1'), 'DAC B = CV_SET into the 1k'),
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        (('U10', '8'), ('U3', '1'), 'ADC on +5V_ISO'), (('U14', '3'), ('R12', '2'), 'LM339 on +12V_ISO'), (('U11', '4'), ('R12', '2'), 'U11 on +12V_ISO'), (('U12', '4'), ('R12', '2'), 'U12 on +12V_ISO'),
        (('U11', '11'), ('U14', '12'), 'U11 V- on AGND'), (('U12', '11'), ('U14', '12'), 'U12 V- on AGND'), (('U12', '12'), ('U14', '12'), 'spare section In+ on AGND'), (('U12', '13'), ('U12', '14'), 'spare section is a follower'),
        (('R12', '1'), ('PS1', '4'), 'filter from the DC-DC output'), (('U3', '3'), ('PS1', '4'), 'LDO from the DC-DC output'), (('PS1', '3'), ('U3', '2'), 'DC-DC return = AGND'),
        (('PS1', '1'), ('J11', '1'), 'DC-DC input = VBUS_LK'), (('J11', '1'), ('J11', '2'), 'both VBUS pins'), (('J10', '1'), ('J1', 'A4'), 'J10 pins 1-2 = VBUS'), (('J10', '2'), ('J1', 'A4'), 'J10 pin 2 = VBUS'),
        (('PS1', '2'), ('J11', '10'), 'DC-DC input return = DGND_LK'), (('J11', '11'), ('J11', '12'), 'DGND_LK pins'), (('J10', '10'), ('J1', 'A1'), 'J10 pins 10-12 = DGND'), (('J10', '12'), ('J1', 'A1'), 'J10 pin 12 = DGND'),
        (('U8', '8'), ('J11', '12'), 'isolator GND1 = DGND_LK'), (('C6', '2'), ('J11', '10'), 'C6 on DGND_LK'), (('R21', '1'), ('J11', '3'), 'pull-ups on +3V3_LK'),
        (('Q1', '2'), ('J1', 'A4'), 'P-FET source on VBUS (no boost)'), (('Q1', '3'), ('J2', '2'), 'P-FET drain to fan +5V'), (('J2', '1'), ('J1', 'A1'), 'fan return = DGND'), (('C3', '1'), ('J1', 'A4'), 'blower bulk cap on VBUS'),
        (('U4', '@PD3'), ('Q2', '1'), 'FAN_EN drives the level shifter'), (('R7', '1'), ('J1', 'A4'), 'P gate pull-up to VBUS'), (('Q2', '3'), ('Q1', '1'), 'level shifter to P gate'),
        (('U4', '@PB9'), ('Q3', '1'), 'FAN_PWM'), (('Q3', '3'), ('J2', '4'), 'open-drain to fan PWM pin'), (('U4', '@PB8'), ('R10', '1'), 'FAN_TACH'), (('R10', '2'), ('J2', '3'), 'from fan tach'),
        # USB
        (('J1', 'A7'), ('D1', '1'), 'D- to ESD'), (('D1', '6'), ('U4', '@PA11'), 'ESD to PA11 (DM)'), (('J1', 'A6'), ('D1', '3'), 'D+ to ESD'), (('D1', '4'), ('U4', '@PA12'), 'ESD to PA12 (DP)'),
        (('J1', 'A5'), ('R1', '1'), 'CC1 pull-down'), (('J1', 'A5'), ('U4', '@PA0'), 'CC1 to PA0'), (('J1', 'B5'), ('U4', '@PA1'), 'CC2 to PA1'),
        (('U1', '1'), ('J1', 'A4'), 'LDO from VBUS'), (('U4', '@VDD'), ('U1', '5'), 'MCU on +3V3'),
        # OLED header and panel LEDs
        (('J5', '3'), ('U4', '@PB6'), 'OLED SCL = PB6'), (('J5', '4'), ('U4', '@PB7'), 'OLED SDA = PB7'), (('R14', '2'), ('J5', '3'), 'SCL pull-up'), (('R15', '2'), ('J5', '4'), 'SDA pull-up'),
        (('R14', '1'), ('U1', '5'), 'pull-ups on +3V3'), (('J5', '2'), ('U1', '5'), 'OLED VCC = +3V3'), (('J5', '1'), ('J1', 'A1'), 'OLED GND = DGND'),
        (('U4', '@PA8'), ('R17', '1'), 'LED_ON from PA8'), (('R17', '2'), ('D5', '2'), 'into the green LED'), (('D5', '1'), ('J1', 'A1'), 'LED cathode to DGND'),
        (('U4', '@PC7'), ('R18', '1'), 'LED_FAULT from PC7'), (('R18', '2'), ('D6', '2'), 'into the red LED'), (('D6', '1'), ('J1', 'A1'), 'LED cathode to DGND'),
        # front panel inputs
        (('ENC1', 'A'), ('U4', '@PB4'), 'encoder A to PB4'), (('ENC1', 'B'), ('U4', '@PB5'), 'encoder B to PB5'), (('ENC1', 'S1'), ('U4', '@PB3'), 'encoder push to PB3'),
        (('R19', '2'), ('U4', '@PB4'), 'pull-up on ENC_A'), (('C24', '1'), ('U4', '@PB4'), 'filter on ENC_A'),
        (('SW3', '1'), ('U4', '@PD0'), 'ON/OFF to PC0'), (('SW4', '1'), ('U4', '@PD1'), 'MODE to PC1'), (('SW5', '1'), ('U4', '@PD2'), 'MENU to PC2'),
        (('SW1', '1'), ('U4', '@PF2'), 'reset button on NRST'), (('J3', '4'), ('U4', '@PF2'), 'SWD NRST'), (('J3', '2'), ('U4', '@PA13'), 'SWDIO'), (('J3', '3'), ('U4', '@PA14'), 'SWCLK'),
        (('SW2', '1'), ('U4', '@PA14'), 'BOOT button on PA14'), (('J4', '2'), ('U4', '@PA9'), 'UART TX'), (('J4', '3'), ('U4', '@PA10'), 'UART RX'),
        (('R16', '1'), ('U4', '@PC6'), 'heartbeat LED on PC6'),
    ]
    for (r1, p1), (r2, p2), why in same:
        a, b = net(r1, p1), net(r2, p2)
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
